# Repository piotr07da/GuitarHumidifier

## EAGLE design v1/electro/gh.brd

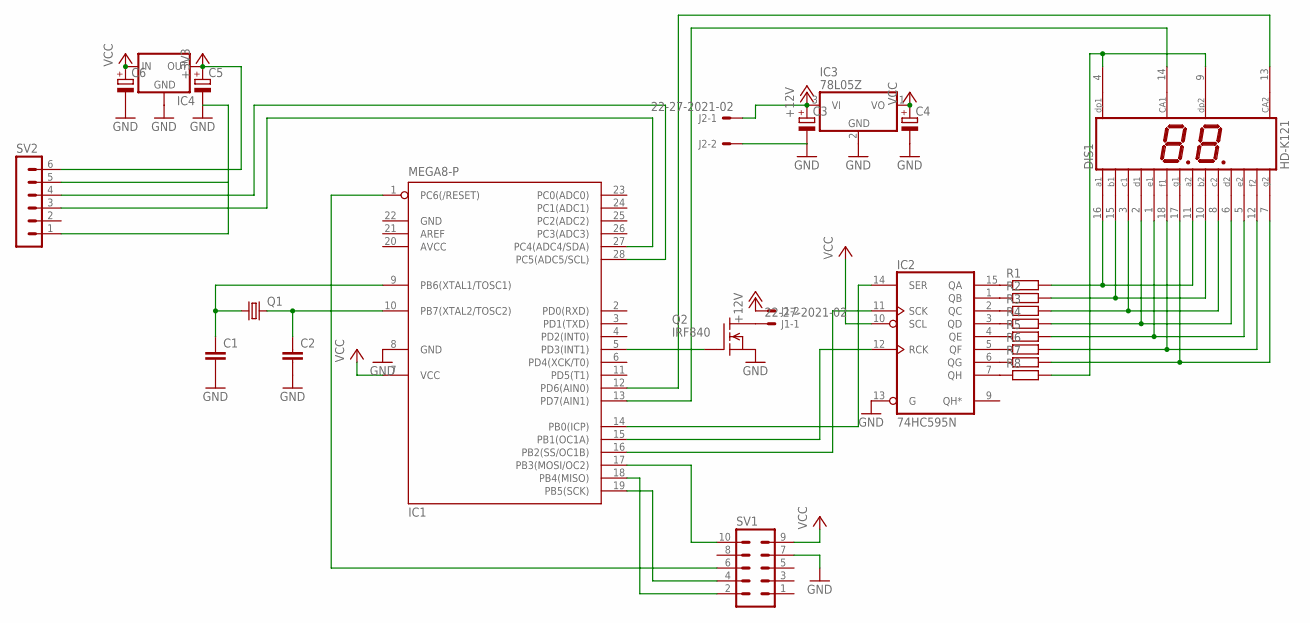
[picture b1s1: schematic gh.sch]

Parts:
C1, C2: C-EU025-024X044; C025-024X044
C3, C4, C5, C6: CPOL-EUE2,5-6E; E2,5-6E
DIS1: HD-K121; HDSP-R
IC1: MEGA8-P; DIL28-3
IC2: 74HC595N; DIL16
IC3: 78L05Z; TO92
IC4: 78LXX
J1, J2: 22-27-2021-02; 6410-02
Q1: CRYSTALHC49U70; HC49U70
Q2: IRF840; TO220
R1, R2, R3, R4, R5, R6, R7, R8: R-EU_0204/2V; 0204V
SV1: MA05-2
SV2: MA06-1

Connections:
+3V3: C5.+, IC4.OUT, SV2.6
+12V: C3.+, IC3.3 (VI), J1.2, J2.1
AVCC: IC1.20 (AVCC)
GND: C1.2, C2.2, C3.-, C4.-, C5.-, C6.-, IC1.8 (GND), IC1.22 (GND), IC2.8 (GND), IC2.13 (G), IC3.2 (GND), IC4.GND, J2.2, Q2.3 (S), SV1.7, SV2.1, SV2.5
unnamed: IC1.14 (PB0(ICP)), IC2.14 (SER)
unnamed: J1.1, Q2.2 (D)
unnamed: IC1.17 (PB3(MOSI/OC2)), SV1.10
unnamed: IC1.18 (PB4(MISO)), SV1.2
unnamed: IC1.1 (PC6(/RESET)), SV1.6
unnamed: IC1.19 (PB5(SCK)), SV1.4
unnamed: C2.1, IC1.10 (PB7(XTAL2/TOSC2)), Q1.2
unnamed: C1.1, IC1.9 (PB6(XTAL1/TOSC1)), Q1.1
unnamed: DIS1.11 (A2), DIS1.16 (A1), R1.2
unnamed: DIS1.10 (B2), DIS1.15 (B1), R2.2
unnamed: DIS1.3 (C1), DIS1.8 (C2), R3.2
unnamed: DIS1.2 (D1), DIS1.6 (D2), R4.2
unnamed: DIS1.1 (E1), DIS1.5 (E2), R5.2
unnamed: DIS1.12 (F2), DIS1.18 (F1), R6.2
unnamed: DIS1.7 (G2), DIS1.17 (G1), R7.2
unnamed: IC2.15 (QA), R1.1
unnamed: IC2.1 (QB), R2.1
unnamed: IC2.2 (QC), R3.1
unnamed: IC2.3 (QD), R4.1
unnamed: IC2.4 (QE), R5.1
unnamed: IC2.5 (QF), R6.1
unnamed: IC2.6 (QG), R7.1
unnamed: IC2.7 (QH), R8.1
unnamed: IC1.5 (PD3(INT1)), Q2.1 (G)
unnamed: DIS1.4 (DP1), DIS1.9 (DP2), R8.2
unnamed: DIS1.14 (CA1), IC1.13 (PD7(AIN1))
unnamed: DIS1.13 (CA2), IC1.12 (PD6(AIN0))
unnamed: IC1.28 (PC5(ADC5/SCL)), SV2.4
unnamed: IC1.27 (PC4(ADC4/SDA)), SV2.3
unnamed: IC1.15 (PB1(OC1A)), IC2.12 (RCK)
unnamed: IC1.16 (PB2(SS/OC1B)), IC2.11 (SCK)
VCC: C4.+, C6.+, IC1.7 (VCC), IC2.10 (SCL), IC2.16 (VCC), IC3.1 (VO), IC4.IN, SV1.9

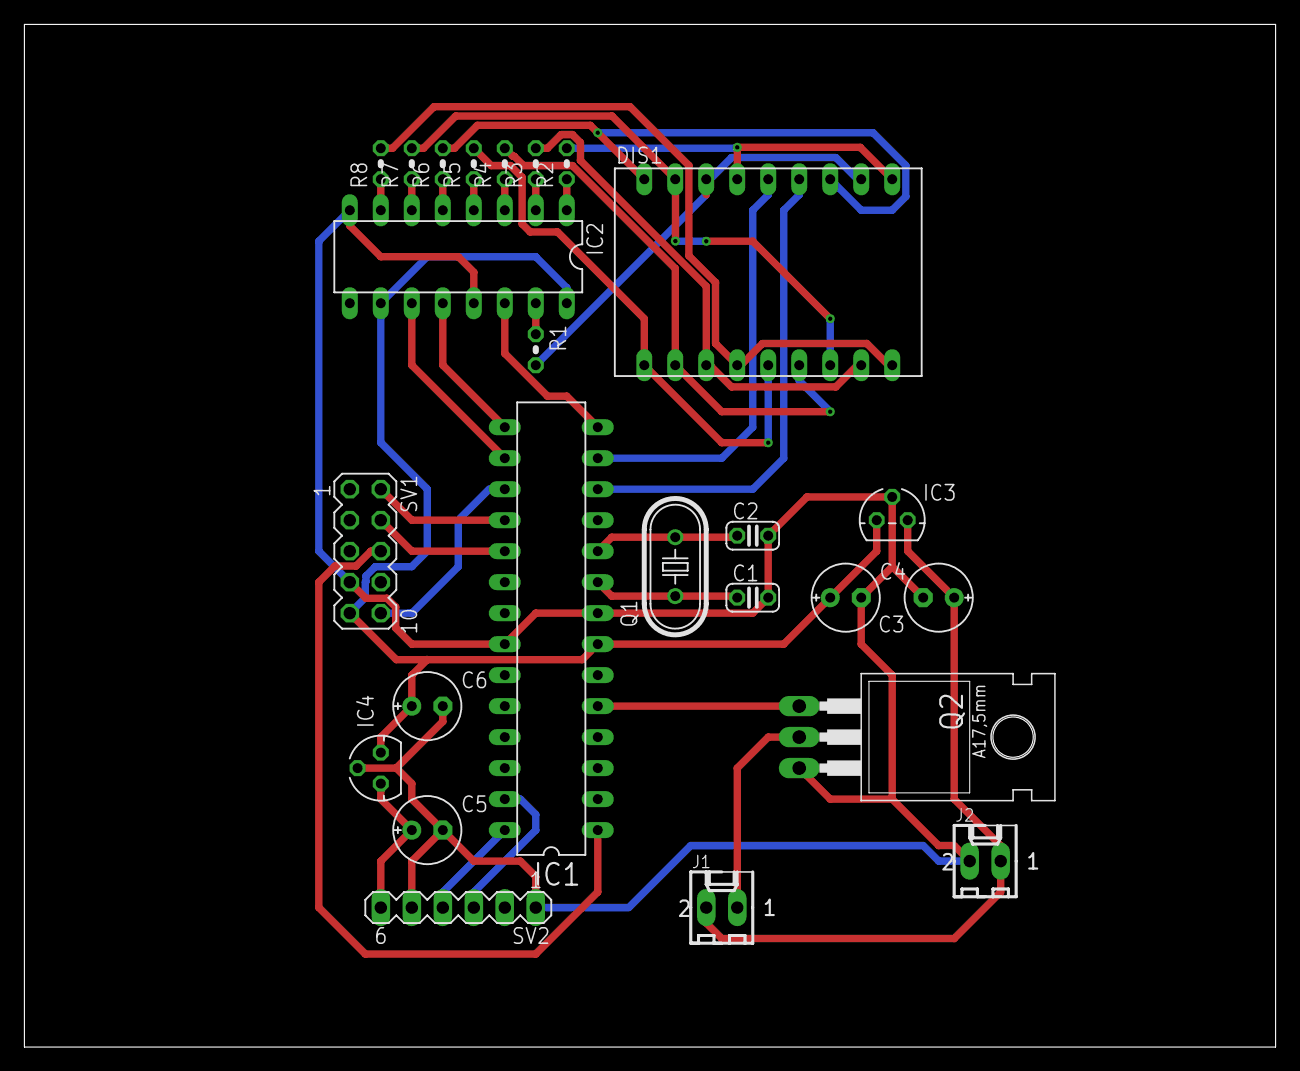
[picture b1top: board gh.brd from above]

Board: 2 copper layers, 102.5 x 83.8 mm, 25 parts (0 on the bottom side), 35 nets.

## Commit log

2018-07-17 działające DHT
2018-07-17 usunięcie DHT
2018-07-20 bme280 - na pewno działa temperatura
2018-08-07 completed
